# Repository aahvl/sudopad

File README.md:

# SudoPad

## A cyberpunk themed sayopad inspired device.

Made for Geometry Dash, Osu, and a ton of other rhythm inspired games, aswell as shortcuts.

Consists of: A OLED Screen, Rotary Encoder and 3 Cherry MX Switches.

### Bill Of Materials

PCB: JLCPCB (£1.49 = jlcpcb.com)
3D Print: 3D People (£11 = https://www.3dmitech.co.uk/instant-quote)
-
OLED Display: AliExpress ([link](https://www.aliexpress.com/item/1005011929267814.html?spm=a2g0o.productlist.main.2.3efaALEAALEA09&algo_pvid=5f7928c2-1e83-4f50-93ee-d873dd05e702&pdp_ext_f=%7B%22order%22%3A%2228%22%2C%22eval%22%3A%221%22%2C%22fromPage%22%3A%22search%22%7D&utparam-url=scene%3Asearch%7Cquery_from%3A%7Cx_object_id%3A1005011929267814%7C_p_origin_prod%3A))
Rotary Encoder: AliExpress ([link](https://www.aliexpress.com/item/1005009718846665.html?spm=a2g0o.productlist.main.2.7a394dc6pBMdYP&algo_pvid=f3579c2a-c1c9-44db-adf0-dfb41b59e461&pdp_ext_f=%7B%22order%22%3A%22114%22%2C%22spu_best_type%22%3A%22price%22%2C%22eval%22%3A%221%22%2C%22fromPage%22%3A%22search%22%7D&utparam-url=scene%3Asearch%7Cquery_from%3A%7Cx_object_id%3A1005009718846665%7C_p_origin_prod%3A))
Cherry MX Switches: AliExpress ([link](https://www.aliexpress.com/item/1005002162885278.html?spm=a2g0o.productlist.main.11.2f50L1eRL1eRm8&algo_pvid=aedab61d-9f6a-4121-a9db-1de0a932894e&pdp_ext_f=%7B%22order%22%3A%2284%22%2C%22spu_best_type%22%3A%22price%22%2C%22eval%22%3A%221%22%2C%22fromPage%22%3A%22search%22%7D&utparam-url=scene%3Asearch%7Cquery_from%3A%7Cx_object_id%3A1005002162885278%7C_p_origin_prod%3A))
KeyCaps: AliExpress ([link](https://www.aliexpress.com/item/1005007484333313.html?spm=a2g0o.productlist.main.1.54ccToCKToCKAx&algo_pvid=da0c0ce8-635a-4fba-9ee8-ceebda2b310d&pdp_ext_f=%7B%22order%22%3A%221705%22%2C%22spu_best_type%22%3A%22price%22%2C%22eval%22%3A%221%22%2C%22fromPage%22%3A%22search%22%7D&utparam-url=scene%3Asearch%7Cquery_from%3A%7Cx_object_id%3A1005007484333313%7C_p_origin_prod%3A))
Seeed Studio XIAO RP2040: AliExpress ([link](https://www.aliexpress.com/item/1005009403509824.html?spm=a2g0o.productlist.main.3.68e96c359lGKG9&algo_pvid=32c3b784-8baa-45b3-828f-13913f067cd7&pdp_ext_f=%7B%22order%22%3A%22-1%22%2C%22eval%22%3A%221%22%2C%22fromPage%22%3A%22search%22%7D&utparam-url=scene%3Asearch%7Cquery_from%3A%7Cx_object_id%3A1005009403509824%7C_p_origin_prod%3A))

Full AliExpress Cart Image (subject to change from offsale items, etc)
Total Price: £29.49

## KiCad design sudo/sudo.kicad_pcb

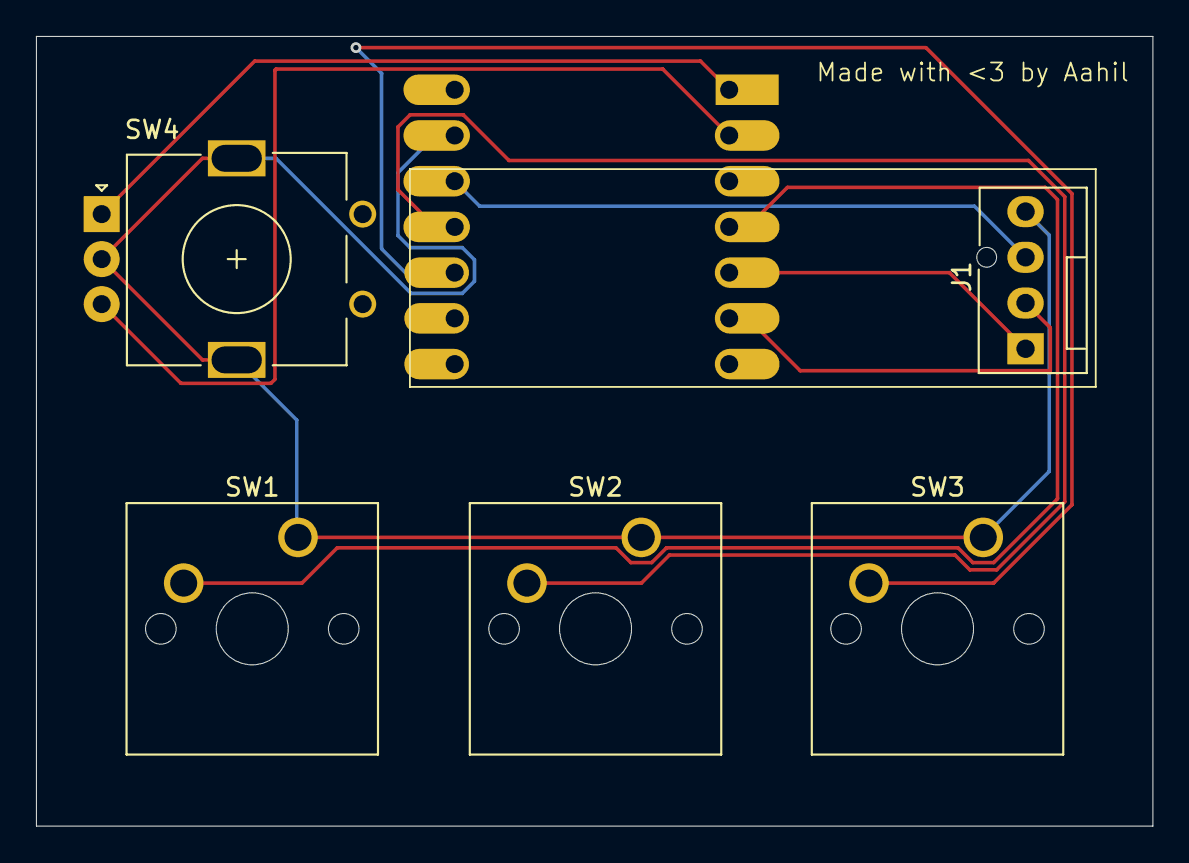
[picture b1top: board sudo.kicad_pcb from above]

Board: 2 copper layers, 62.0 x 43.9 mm, 6 parts (1 on the bottom side), 9 nets.

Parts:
J1: OLED_DISP; FanPinHeader_1x04_P2.54mm_Vertical
SW1: Key1; SW_Cherry_MX_1.00u_PCB
SW2: Key2; SW_Cherry_MX_1.00u_PCB
SW3: Key3; SW_Cherry_MX_1.00u_PCB
SW4: RotaryEncoder_Switch_MP; RotaryEncoder_Alps_EC11E_Vertical_H20mm
U1: MOUDLE-SEEEDUINO-XIAO; XIAO-Generic-Hybrid-14P-2.54-21X17.8MM

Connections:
+3V3: J1.2, U1.12 (3V3)
GND: J1.1, SW1.1, SW2.1, SW3.1, SW4.C, SW4.MP, U1.13 (GND)
KeyNum1: SW1.2, U1.4 (PA11_A3_D3)
KeyNum2: SW2.2, U1.11 (PA6_A10_D10_MOSI)
KeyNum3: SW3.2, U1.10 (PA5_A9_D9_MISO)
unnamed: J1.3, U1.6 (PA9_A5_D5_SCL)
unnamed: J1.4, U1.5 (PA8_A4_D4_SDA)
unnamed: SW4.A, U1.1 (PA02_A0_D0)
unnamed: SW4.B, U1.2 (PA4_A1_D1)

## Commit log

2026-05-28 Initialize README with project details and images
    Added project description, images, and Bill of Materials section.
2026-05-29 FINALLY THE GODLY FILES
    WOWZERS
2026-05-29 new sudo pcb!
2026-05-29 NEW pcb photo
